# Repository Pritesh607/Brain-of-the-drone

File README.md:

# Brain-of-the-drone
A cool flight controller for drone with brushed motors with inbuilt motor driver made using esp32 and can be controlled using wifi or your transmitter with the betafpv firmware.
If we come to the esp32 model i used in this project is an esp32 S3 by Xiao Speed studio, i could have also used esp32 C3 or even an esp8266 which are comparatively cheaper than the esp32 S3 i used but they lake the performance that esp32 S3 gives because I also want to fly the drone with Betafpv firmware as an FPV drone which need a lot faster processing time which an esp32 S3 can deliver and there are many sensors to read but for now i didn't added ant extra sensor except mpu6050 because it will make this project more complex and costlier and here is a comparison between an esp32 C3 and esp32 S3 to show the clear difference: 

-CPU Architecture
Esp32 C3:32-bit RISC-V (Open-source)	CPU Architecture
Esp32 S3:32-bit Xtensa LX7
-CPU Cores
Esp32 C3:Single-core	CPU Cores
Esp32 S3:Dual-core
-Max Clock Speed
Esp32 C3:160 MHz	Max Clock Speed
Esp32 S3:240 MHz
-SRAM (Internal)
Esp32 C3:400 KB	SRAM (Internal)
Esp32 S3:512 KB
-Available GPIOs
Esp32 C3:22	Available GPIOs
Esp32 S3:45

Now if we come to the hardware part, we will use 816 coreless motor or any comparable coreless motor for more thrust and we will not require any external motor driver as it is inbuild into the flight controller and for the frame we can use any small drone frame that can fit all the components and will be stable and for the battery we will use an 1s lipo battery.  

For the Wi-Fi controlled drone firmware you can see the video "ESP32 WI-FI CONTROLLED DRONE from scratch tutorial" by Dr Electronics on YouTube because it is a long process. Now for the Betafpv firmware you just have to flash the Betafpv compatable firmware onto the Esp32 S3 which i have given and install the betafpv v10.10.   

NOTE: To give power to the Esp32 you have to directly solder a wire to the back of the esp32 s3 because there is a external battery connector and you can charge the battery directly from the esp32 Type-C connector.
## PCB Design
[View or Download bom.csv](./bom%20(1).csv)

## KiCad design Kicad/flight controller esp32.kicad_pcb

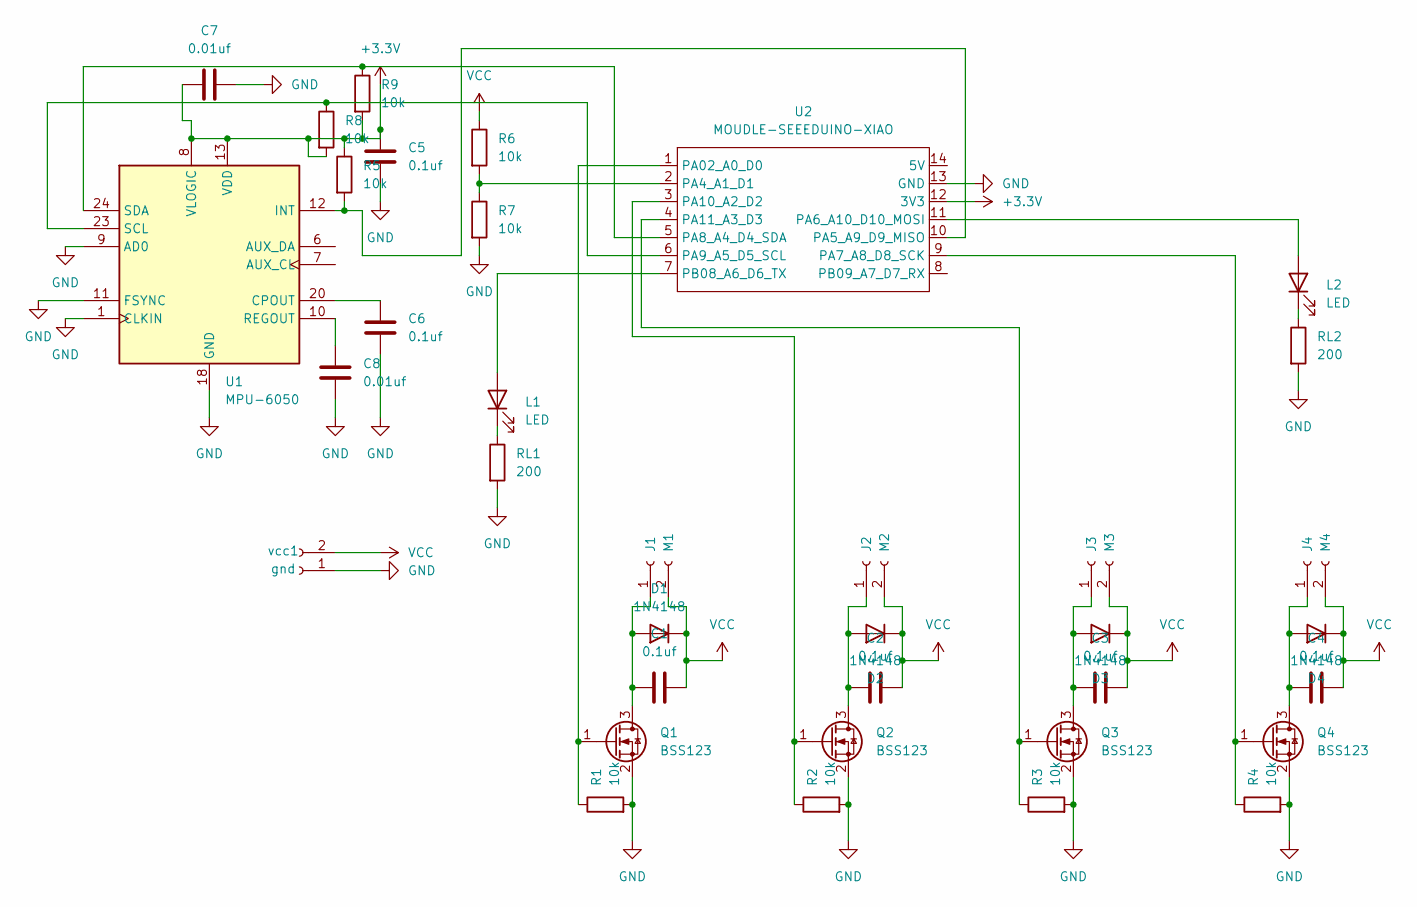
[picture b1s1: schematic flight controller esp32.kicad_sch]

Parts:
C1, C2, C3, C4, C5, C6: 0.1uf; C_0805_2012Metric_Pad1.18x1.45mm_HandSolder
C7, C8: 0.01uf; C_0805_2012Metric_Pad1.18x1.45mm_HandSolder
D1, D2, D3, D4: 1N4148; D_SOD-123
J1: M1; SolderWire-0.15sqmm_1x02_P4mm_D0.5mm_OD1.5mm
J2: M2; SolderWire-0.15sqmm_1x02_P4mm_D0.5mm_OD1.5mm
J3: M3; SolderWire-0.15sqmm_1x02_P4mm_D0.5mm_OD1.5mm
J4: M4; SolderWire-0.15sqmm_1x02_P4mm_D0.5mm_OD1.5mm
L1, L2: LED; C_0805_2012Metric_Pad1.18x1.45mm_HandSolder
Q1, Q2, Q3, Q4: BSS123; SOT-23
R1, R2, R3, R4, R5, R6, R7, R8, R9: 10k; C_0805_2012Metric_Pad1.18x1.45mm_HandSolder
RL1, RL2: 200; C_0805_2012Metric_Pad1.18x1.45mm_HandSolder
U1: MPU-6050; InvenSense_QFN-24_4x4mm_P0.5mm
U2: MOUDLE-SEEEDUINO-XIAO; MODULE_XIAO_ESP32_S3
vcc1: gnd; JST_XH_S2B-XH-A_1x02_P2.50mm_Horizontal

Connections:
+3.3V: C5.1, C7.1, R5.1, R8.2, R9.2, U1.8 (VLOGIC), U1.13 (VDD), U2.12 (3V3)
GND: C5.2, C6.2, C7.2, C8.2, Q1.2 (S), Q2.2 (S), Q3.2 (S), Q4.2 (S), R1.2, R2.2, R3.2, R4.2, R7.2, RL1.2, RL2.2, U1.1 (CLKIN), U1.9 (AD0), U1.11 (FSYNC), U1.18 (GND), U2.13 (GND), vcc1.1
unnamed: C1.1, D1.2 (A), J1.1, Q1.3 (D)
unnamed: C2.1, D2.2 (A), J2.1, Q2.3 (D)
unnamed: C3.1, D3.2 (A), J3.1, Q3.3 (D)
unnamed: C4.1, D4.2 (A), J4.1, Q4.3 (D)
unnamed: L1.2 (A), U2.7 (PB08_A6_D6_TX)
unnamed: L1.1 (K), RL1.1
unnamed: L2.2 (A), U2.11 (PA6_A10_D10_MOSI)
unnamed: L2.1 (K), RL2.1
unnamed: Q1.1 (G), R1.1, U2.1 (PA02_A0_D0)
unnamed: Q2.1 (G), R2.1, U2.3 (PA10_A2_D2)
unnamed: Q3.1 (G), R3.1, U2.4 (PA11_A3_D3)
unnamed: Q4.1 (G), R4.1, U2.9 (PA7_A8_D8_SCK)
unnamed: C6.1, U1.20 (CPOUT)
unnamed: R5.2, U1.12 (INT), U2.10 (PA5_A9_D9_MISO)
unnamed: C8.1, U1.10 (REGOUT)
unnamed: R8.1, U1.23 (SCL), U2.6 (PA9_A5_D5_SCL)
unnamed: R9.1, U1.24 (SDA), U2.5 (PA8_A4_D4_SDA)
unnamed: R6.2, R7.1, U2.2 (PA4_A1_D1)
VCC: C1.2, C2.2, C3.2, C4.2, D1.1 (K), D2.1 (K), D3.1 (K), D4.1 (K), J1.2, J2.2, J3.2, J4.2, R6.1, vcc1.2

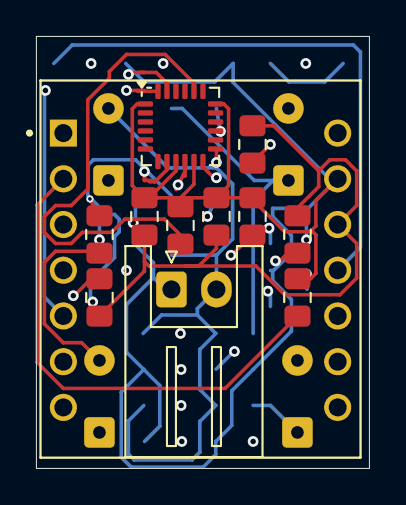
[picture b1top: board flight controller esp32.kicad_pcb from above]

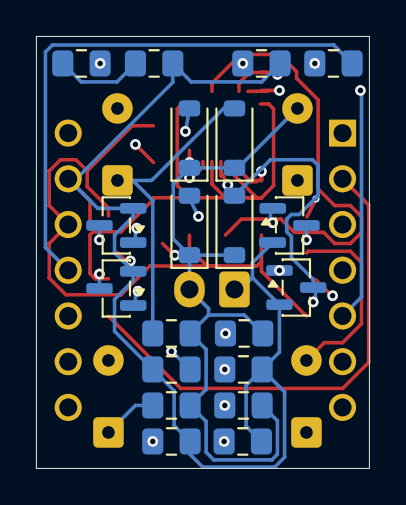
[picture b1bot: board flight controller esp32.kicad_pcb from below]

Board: 4 copper layers, 18.5 x 24.0 mm, 36 parts (20 on the bottom side), 21 nets.

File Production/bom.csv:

"Reference","Qty","Value","DNP","Exclude from BOM","Exclude from Board","Footprint","Datasheet"
"C1,C2,C3,C4,C5,C6","6","0.1uf","","","","Capacitor_SMD:C_0805_2012Metric_Pad1.18x1.45mm_HandSolder",""
"C7,C8","2","0.01uf","","","","Capacitor_SMD:C_0805_2012Metric_Pad1.18x1.45mm_HandSolder",""
"D1,D2,D3,D4","4","1N4148","","","","Diode_SMD:D_SOD-123","https://assets.nexperia.com/documents/data-sheet/1N4148_1N4448.pdf"
"J1","1","M1","","","","Connector_Wire:SolderWire-0.15sqmm_1x02_P4mm_D0.5mm_OD1.5mm",""
"J2","1","M2","","","","Connector_Wire:SolderWire-0.15sqmm_1x02_P4mm_D0.5mm_OD1.5mm",""
"J3","1","M3","","","","Connector_Wire:SolderWire-0.15sqmm_1x02_P4mm_D0.5mm_OD1.5mm",""
"J4","1","M4","","","","Connector_Wire:SolderWire-0.15sqmm_1x02_P4mm_D0.5mm_OD1.5mm",""
"L1,L2","2","LED","","","","Capacitor_SMD:C_0805_2012Metric_Pad1.18x1.45mm_HandSolder",""
"Q1,Q2,Q3,Q4","4","BSS123","","","","Package_TO_SOT_SMD:SOT-23","http://www.diodes.com/assets/Datasheets/ds30366.pdf"
"R1,R2,R3,R4,R5,R6,R7,R8,R9","9","10k","","","","Capacitor_SMD:C_0805_2012Metric_Pad1.18x1.45mm_HandSolder",""
"RL1,RL2","2","200","","","","Capacitor_SMD:C_0805_2012Metric_Pad1.18x1.45mm_HandSolder",""
"U1","1","MPU-6050","","","","Sensor_Motion:InvenSense_QFN-24_4x4mm_P0.5mm","https://invensense.tdk.com/wp-content/uploads/2015/02/MPU-60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"
"U2","1","MOUDLE-SEEEDUINO-XIAO","","","","XIAO_ESP32_S3:MODULE_XIAO_ESP32_S3",""
"vcc1","1","gnd","","","","Connector_JST:JST_XH_S2B-XH-A_1x02_P2.50mm_Horizontal",""
